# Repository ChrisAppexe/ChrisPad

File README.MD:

Inspiration:
	I wanted to create a personal micropad to assist me with everyday tasks(Copy,paste,etc...) but also look cool enough(having a small knob etc)
Challenges:
	I had never heard about kicad but thankfully it was easy to understand
Specifications

BOM:

8x Cherry MX Switches
2x SK6812 MINI Leds
1x XIAO RP2040
8x Blank DSA Keycaps
4x M3x16 Bolt
4x M3 Heatset
1x EC11 Rotary Encoder

Others:

ChrisPad Base.step 
ChrisPad Top.step 
ChrisPadVolumeknob.stl

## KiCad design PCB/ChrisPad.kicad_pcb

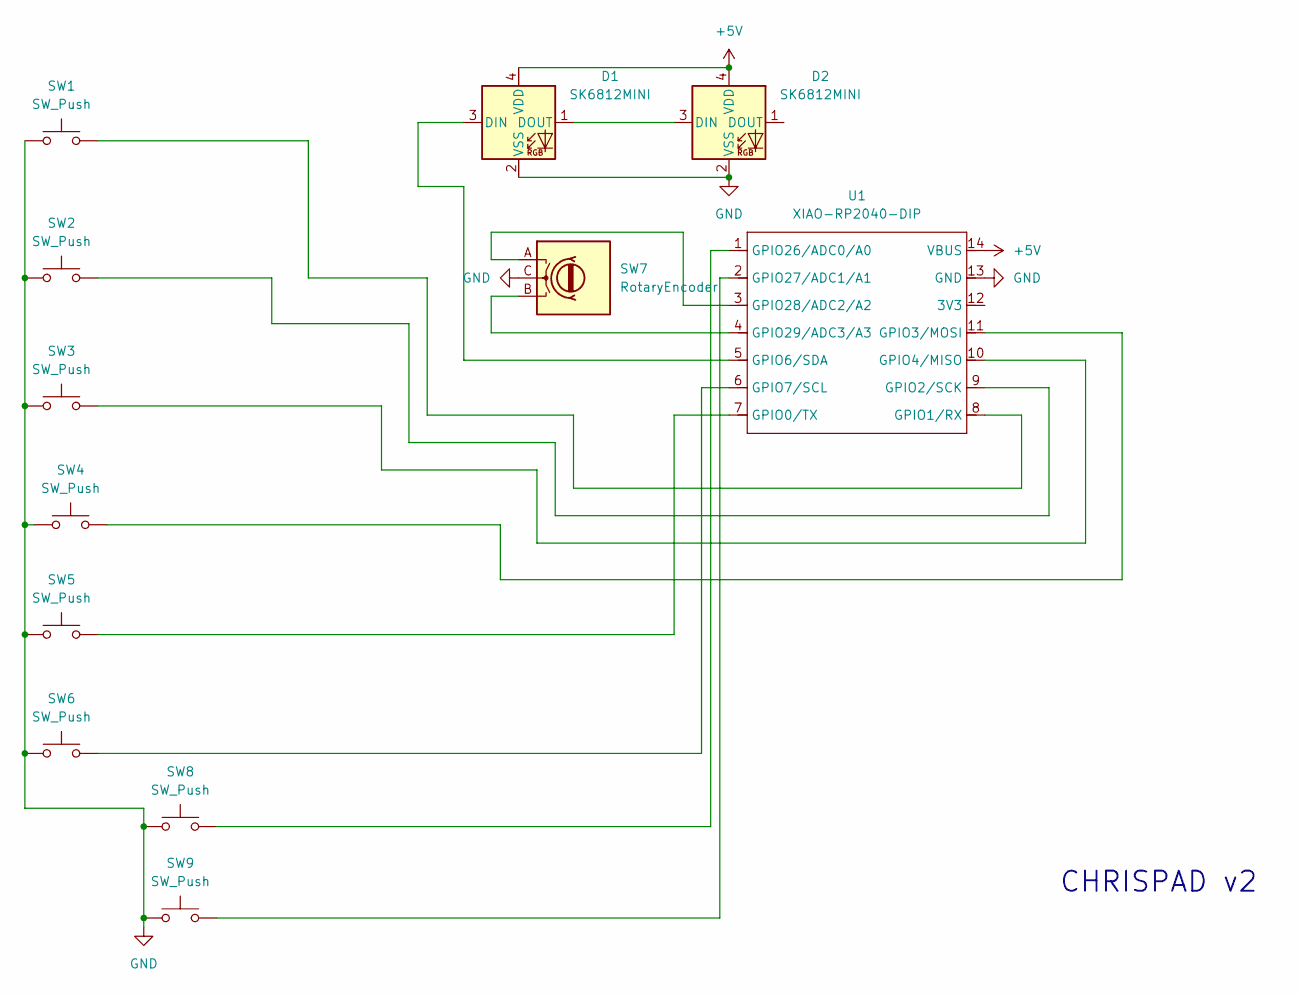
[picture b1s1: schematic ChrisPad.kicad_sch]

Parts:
D1, D2: SK6812MINI; LED_SK6812MINI_PLCC4_3.5x3.5mm_P1.75mm
SW1, SW2, SW3, SW4, SW5, SW6, SW8, SW9: SW_Push; SW_Cherry_MX_1.00u_PCB
SW7: RotaryEncoder; RotaryEncoder_Alps_EC11E-Switch_Vertical_H20mm
U1: XIAO-RP2040-DIP

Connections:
+5V: D1.4 (VDD), D2.4 (VDD), U1.14 (VBUS)
GND: D1.2 (VSS), D2.2 (VSS), SW1.1, SW2.1, SW3.1, SW4.1, SW5.1, SW6.1, SW7.C, SW8.1, SW9.1, U1.13 (GND)
unnamed: D1.3 (DIN), U1.5 (GPIO6/SDA)
unnamed: D1.1 (DOUT), D2.3 (DIN)
unnamed: SW5.2, U1.7 (GPIO0/TX)
unnamed: SW1.2, U1.8 (GPIO1/RX)
unnamed: SW2.2, U1.9 (GPIO2/SCK)
unnamed: SW4.2, U1.11 (GPIO3/MOSI)
unnamed: SW3.2, U1.10 (GPIO4/MISO)
unnamed: SW6.2, U1.6 (GPIO7/SCL)
unnamed: SW8.2, U1.1 (GPIO26/ADC0/A0)
unnamed: SW9.2, U1.2 (GPIO27/ADC1/A1)
unnamed: SW7.A, U1.3 (GPIO28/ADC2/A2)
unnamed: SW7.B, U1.4 (GPIO29/ADC3/A3)

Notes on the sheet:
CHRISPAD v2

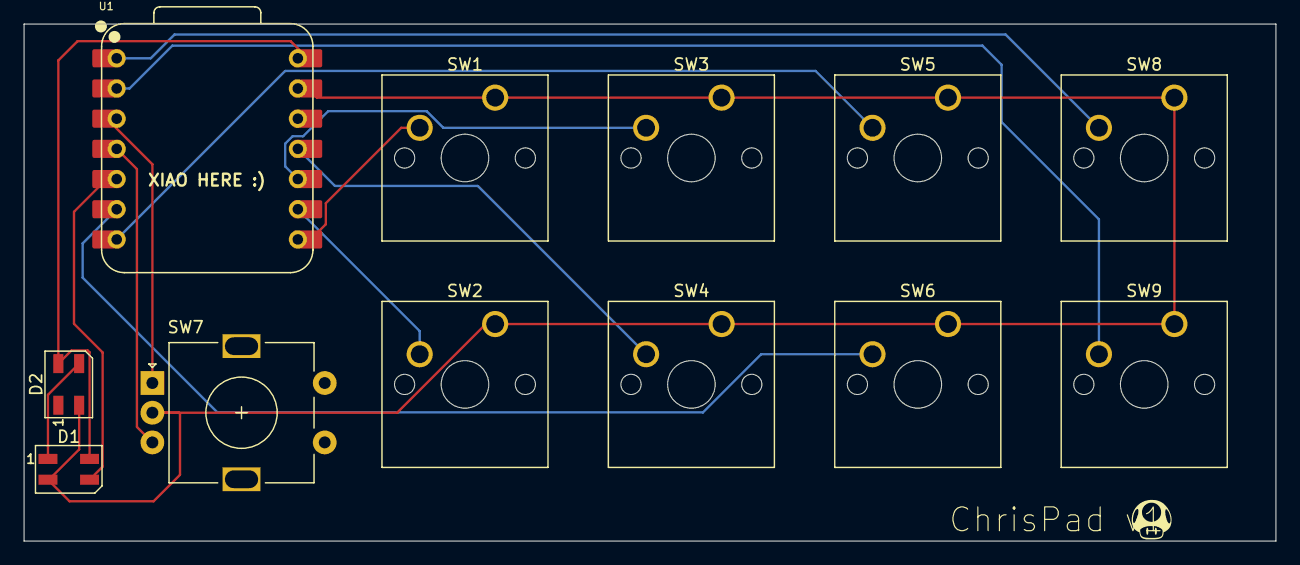
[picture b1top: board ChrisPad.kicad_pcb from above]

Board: 2 copper layers, 105.3 x 43.5 mm, 13 parts (0 on the bottom side), 14 nets.

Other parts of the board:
Mush: LOGO; mus3x3

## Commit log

2025-12-06 Create CAD
